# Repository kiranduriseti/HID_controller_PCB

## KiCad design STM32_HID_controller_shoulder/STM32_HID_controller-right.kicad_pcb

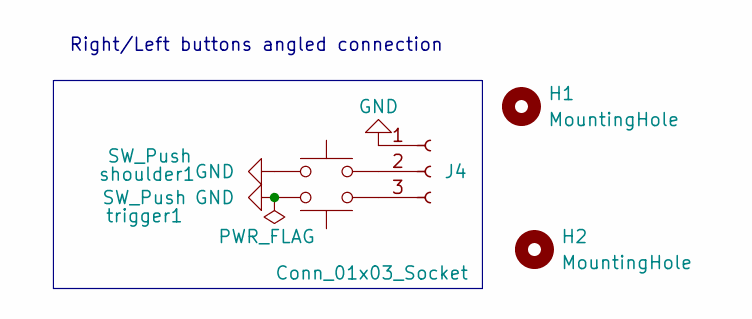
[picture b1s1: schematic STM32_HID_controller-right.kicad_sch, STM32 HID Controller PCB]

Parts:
H1, H2: MountingHole; MountingHole_2.2mm_M2
J4: Conn_01x03_Socket; JST_EH_S3B-EH_1x03_P2.50mm_Horizontal
shoulder1: SW_Push; SW_PUSH-12mm_Wuerth-430476085716
trigger1: SW_Push; SW_DIP_SPSTx01_Piano_10.8x4.1mm_W7.62mm_P2.54mm

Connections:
GND: J4.1, shoulder1.2, trigger1.1
unnamed: J4.2, shoulder1.1
unnamed: J4.3, trigger1.2

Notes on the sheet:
Right/Left buttons angled connection

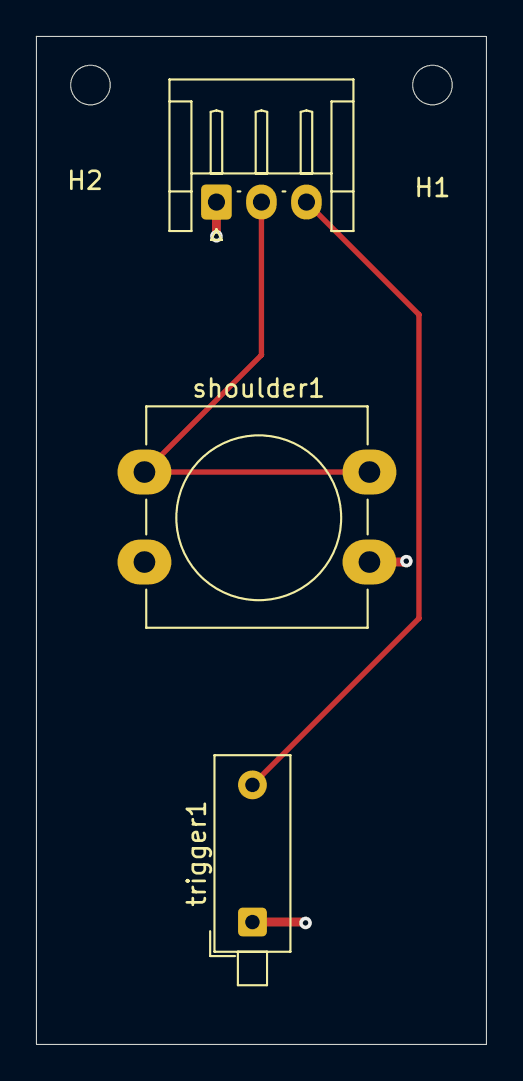
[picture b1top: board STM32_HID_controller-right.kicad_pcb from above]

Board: 2 copper layers, 25.0 x 56.0 mm, 5 parts (0 on the bottom side), 3 nets.

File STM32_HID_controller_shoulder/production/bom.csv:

Designator,Footprint,Quantity,Value,LCSC Part #
J4,JST_EH_S3B-EH_1x03_P2.50mm_Horizontal,1,Conn_01x03_Socket,
SHOULDER1,SW_PUSH-12mm_Wuerth-430476085716,1,SW_Push,
TRIGGER1,SW_DIP_SPSTx01_Piano_10.8x4.1mm_W7.62mm_P2.54mm,1,SW_Push,

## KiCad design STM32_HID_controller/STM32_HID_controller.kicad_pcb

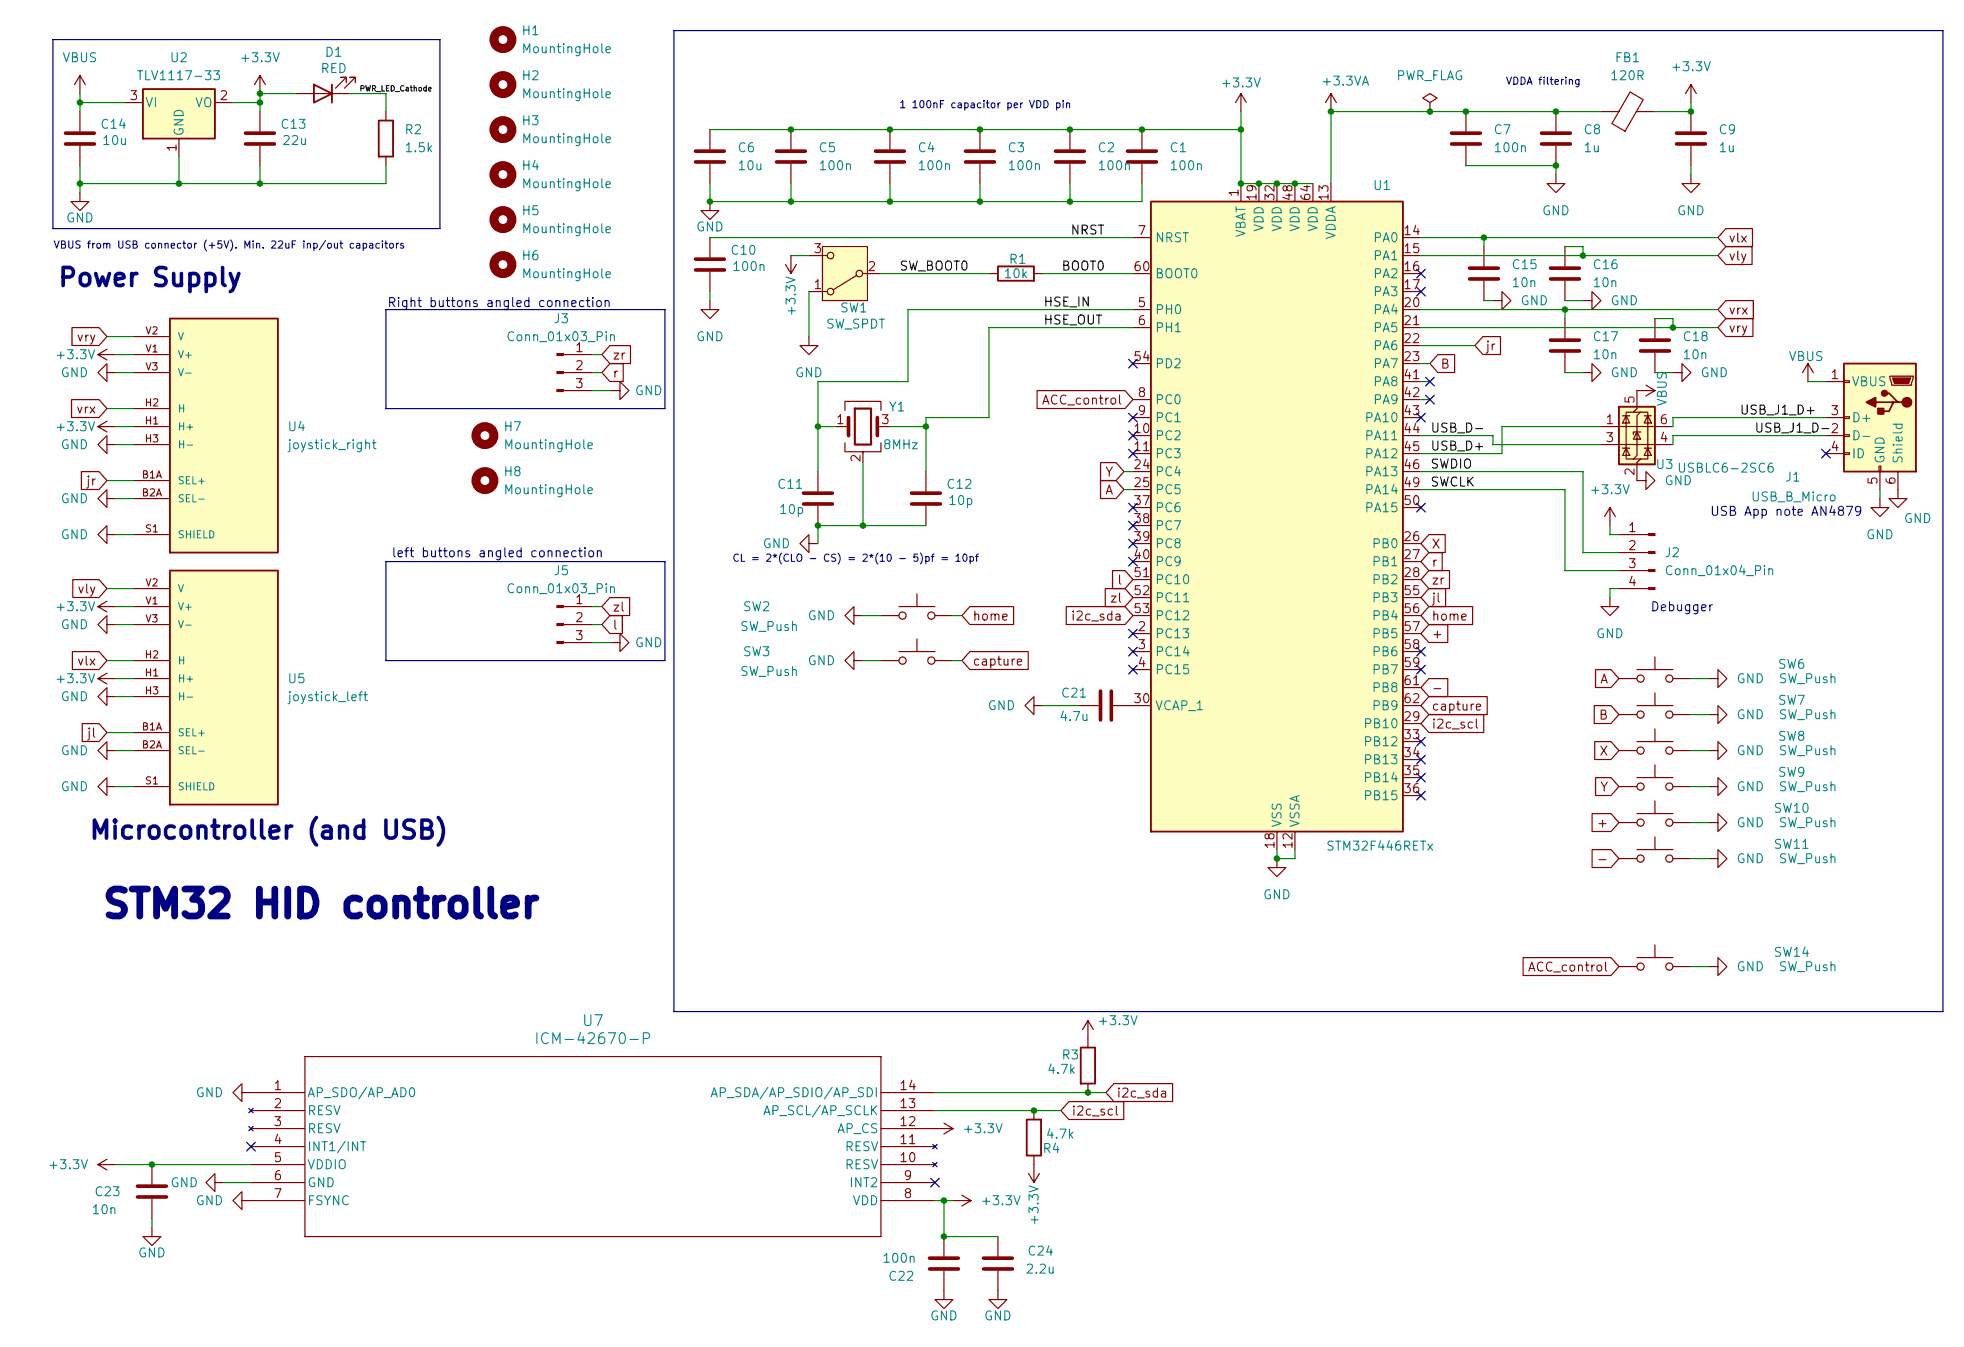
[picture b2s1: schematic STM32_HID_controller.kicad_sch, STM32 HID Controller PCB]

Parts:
C1, C2, C3, C4, C5, C7, C10, C22: 100n; C_0402_1005Metric; MPN GRM155R71C104KA88D
C6: 10u; C_0603_1608Metric; MPN C1608X5R1A106K080AC
C8, C9: 1u; C_0402_1005Metric; MPN CC0402KRX5R6BB105
C11, C12: 10p; C_0402_1005Metric; MPN GRM1555C1H100JA01D
C13: 22u; C_0805_2012Metric; MPN C0805C226M8PACTU
C14: 10u; C_0805_2012Metric; MPN C0805C106M8PACTU
C15, C16, C17, C18, C23: 10n; C_0402_1005Metric; MPN GRM155R71C103KA01D
C21: 4.7u; C_0603_1608Metric; MPN C0603C475K8PACTU
C24: 2.2u; C_0201_0603Metric; MPN GRM033R60J225ME47D
D1: RED; LED_0603_1608Metric; MPN LTST-C190KRKT
FB1: 120R; L_0603_1608Metric; MPN BLM18AG121SN1D
H1, H3, H7, H8: MountingHole; MountingHole_2.2mm_M2
H2, H4, H5, H6: MountingHole; MountingHole_3.2mm_M3
J1: USB_B_Micro; USB_Micro-B_Wuerth_629105150521; MPN 629105150521
J2: Conn_01x04_Pin; PinHeader_1x04_P2.54mm_Vertical; MPN 61300411121
J3, J5: Conn_01x03_Pin; JST_EH_S3B-EH_1x03_P2.50mm_Horizontal; MPN S3B-EH(LF)(SN)
R1: 10k; R_0402_1005Metric; MPN RC0402FR-0710KL
R2: 1.5k; R_0402_1005Metric; MPN RC0402FR-071K5L
R3, R4: 4.7k; R_0402_1005Metric; MPN RC0402FR-074K7L
SW1: SW_SPDT; SW_SPDT_PCM12; MPN PCM12SMTR
SW2, SW3, SW10, SW11, SW14: SW_Push; SW_PUSH_6mm; MPN B3F-1000
SW6, SW7, SW8, SW9: SW_Push; SW_PUSH-12mm_Wuerth-430476085716; MPN 430476085716
U1: STM32F446RETx; LQFP-64_10x10mm_P0.5mm; MPN STM32F446RET6
U2: TLV1117-33; SOT-223-3_TabPin2; MPN TLV1117LV33DCYR
U3: USBLC6-2SC6; SOT-23-6; MPN USBLC6-2SC6
U4: joystick_right; XDCR_COM-09032; PARTREV N/A
U5: joystick_left; XDCR_COM-09032; PARTREV N/A
U7: ICM-42670-P; LGA14_2.5X3X0.76_IVS-M; MPN ICM-42670-P
Y1: 8MHz; Crystal_SMD_3225-4Pin_3.2x2.5mm; MPN J32SMX-H-F-G-I-8M0

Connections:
+: SW10.1, U1.57 (PB5)
+3.3V: C1.1, C2.1, C3.1, C4.1, C5.1, C6.1, C9.1, C13.1, C22.2, C23.2, C24.1, D1.2 (A), FB1.2, J2.1, R3.1, R4.1, SW1.3 (C), U1.1 (VBAT), U1.19 (VDD), U1.32 (VDD), U1.48 (VDD), U1.64 (VDD), U2.2 (VO), U4.H1 (H+), U4.V1 (V+), U5.H1 (H+), U5.V1 (V+), U7.5 (VDDIO), U7.8 (VDD), U7.12 (AP_CS)
+3.3VA: C7.1, C8.1, FB1.1, U1.13 (VDDA)
-: SW11.1, U1.61 (PB8)
/BOOT0: R1.2, U1.60 (BOOT0)
/HSE_IN: C11.1, U1.5 (PH0), Y1.1
/HSE_OUT: C12.1, U1.6 (PH1), Y1.3
/NRST: C10.1, U1.7 (NRST)
/PWR_LED_Cathode: D1.1 (K), R2.1
/SWCLK: J2.3, U1.49 (PA14)
/SWDIO: J2.2, U1.46 (PA13)
/SW_BOOT0: R1.1, SW1.2 (B)
/USB_D+: U1.45 (PA12), U3.1 (I/O1)
/USB_D-: U1.44 (PA11), U3.3 (I/O2)
/USB_J1_D+: J1.3 (D+), U3.6 (I/O1)
/USB_J1_D-: J1.2 (D-), U3.4 (I/O2)
A: SW6.1, U1.25 (PC5)
ACC_control: SW14.1, U1.8 (PC0)
B: SW7.1, U1.23 (PA7)
GND: C1.2, C2.2, C3.2, C4.2, C5.2, C6.2, C7.2, C8.2, C9.2, C10.2, C11.2, C12.2, C13.2, C14.2, C15.2, C16.2, C17.2, C18.2, C21.1, C22.1, C23.1, C24.2, J1.5 (GND), J1.6 (Shield), J2.4, J3.3, J5.3, R2.2, SW1.1 (A), SW2.1, SW3.1, SW6.2, SW7.2, SW8.2, SW9.2, SW10.2, SW11.2, SW14.2, U1.12 (VSSA), U1.18 (VSS), U1.31 (VSS), U1.47 (VSS), U1.63 (VSS), U2.1 (GND), U3.2 (GND), U4.B2A (SEL-), U4.H3 (H-), U4.S1 (SHIELD), U4.S2 (SHIELD), U4.S3 (SHIELD), U4.S4 (SHIELD), U4.V3 (V-), U5.B2A (SEL-), U5.H3 (H-), U5.S1 (SHIELD), U5.S2 (SHIELD), U5.S3 (SHIELD), U5.S4 (SHIELD), U5.V3 (V-), U7.1 (AP_SDO/AP_AD0), U7.6 (GND), U7.7 (FSYNC), Y1.2 (G), Y1.4 (G)
unnamed: C21.2, U1.30 (VCAP_1)
VBUS: C14.1, J1.1 (VBUS), U2.3 (VI), U3.5 (VBUS)
X: SW8.1, U1.26 (PB0)
Y: SW9.1, U1.24 (PC4)
capture: SW3.2, U1.62 (PB9)
home: SW2.2, U1.56 (PB4)
i2c_scl: R4.2, U1.29 (PB10), U7.13 (AP_SCL/AP_SCLK)
i2c_sda: R3.2, U1.53 (PC12), U7.14 (AP_SDA/AP_SDIO/AP_SDI)
jl: U1.55 (PB3), U5.B1A (SEL+)
jr: U1.22 (PA6), U4.B1A (SEL+)
l: J5.2, U1.51 (PC10)
r: J3.2, U1.27 (PB1)
vlx: C15.1, U1.14 (PA0), U5.H2 (H)
vly: C16.1, U1.15 (PA1), U5.V2 (V)
vrx: C17.1, U1.20 (PA4), U4.H2 (H)
vry: C18.1, U1.21 (PA5), U4.V2 (V)
zl: J5.1, U1.52 (PC11)
zr: J3.1, U1.28 (PB2)

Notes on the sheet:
1 100nF capacitor per VDD pin
VDDA filtering
Debugger
Microcontroller (and USB)
Power Supply
CL = 2*(CLO - CS) = 2*(10 - 5)pf = 10pf
USB App note AN4879
left buttons angled connection
Right buttons angled connection
STM32 HID controller
VBUS from USB connector (+5V). Min. 22uF inp/out capacitors

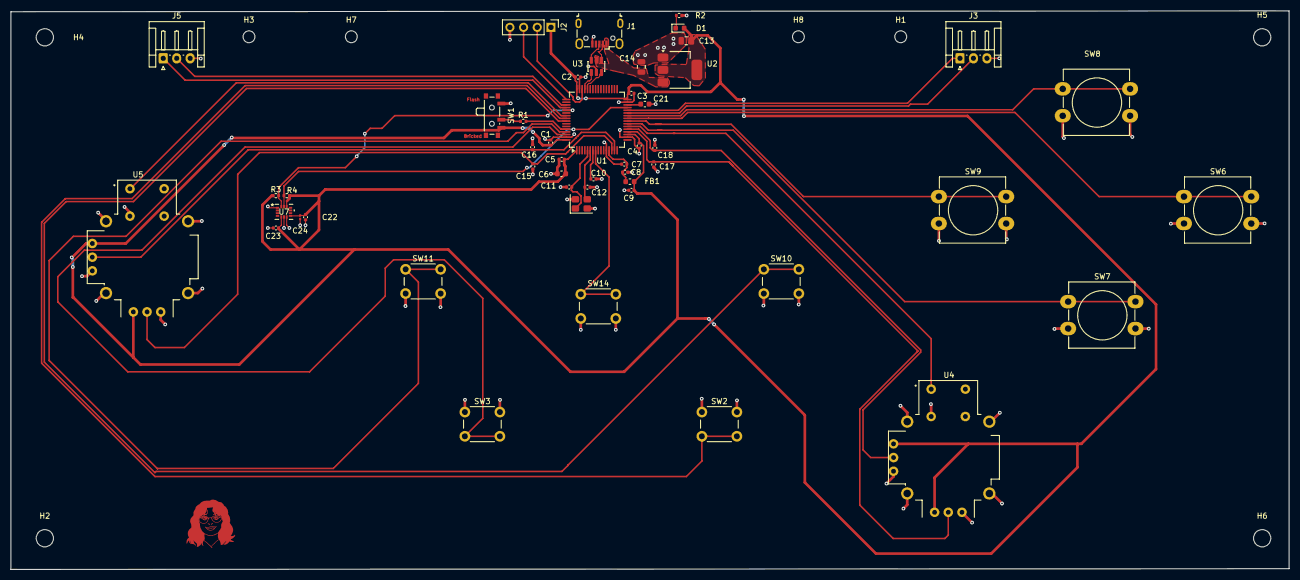
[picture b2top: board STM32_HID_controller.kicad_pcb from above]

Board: 2 copper layers, 237.3 x 103.7 mm, 57 parts (0 on the bottom side), 38 nets.

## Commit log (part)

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2026-01-08 Seperated PCBs
2026-01-08 Started flux
2026-01-09 Started flux for left and right
2026-01-09 added gnd vias shortend sclk
2026-01-10 main pcb finished
2026-01-10 Shoulder finished
2026-01-10 final draft
2026-01-10 changed shoulder to right orientation
2026-01-10 changed 3.3V mapping
2026-01-10 added text
2026-01-10 changed 3.3V routing
2026-01-16 added mpu
2026-01-17 mpu6050 pull ups
2026-01-17 added mpu to everything, final draft before review
2026-01-19 Manufacturing
